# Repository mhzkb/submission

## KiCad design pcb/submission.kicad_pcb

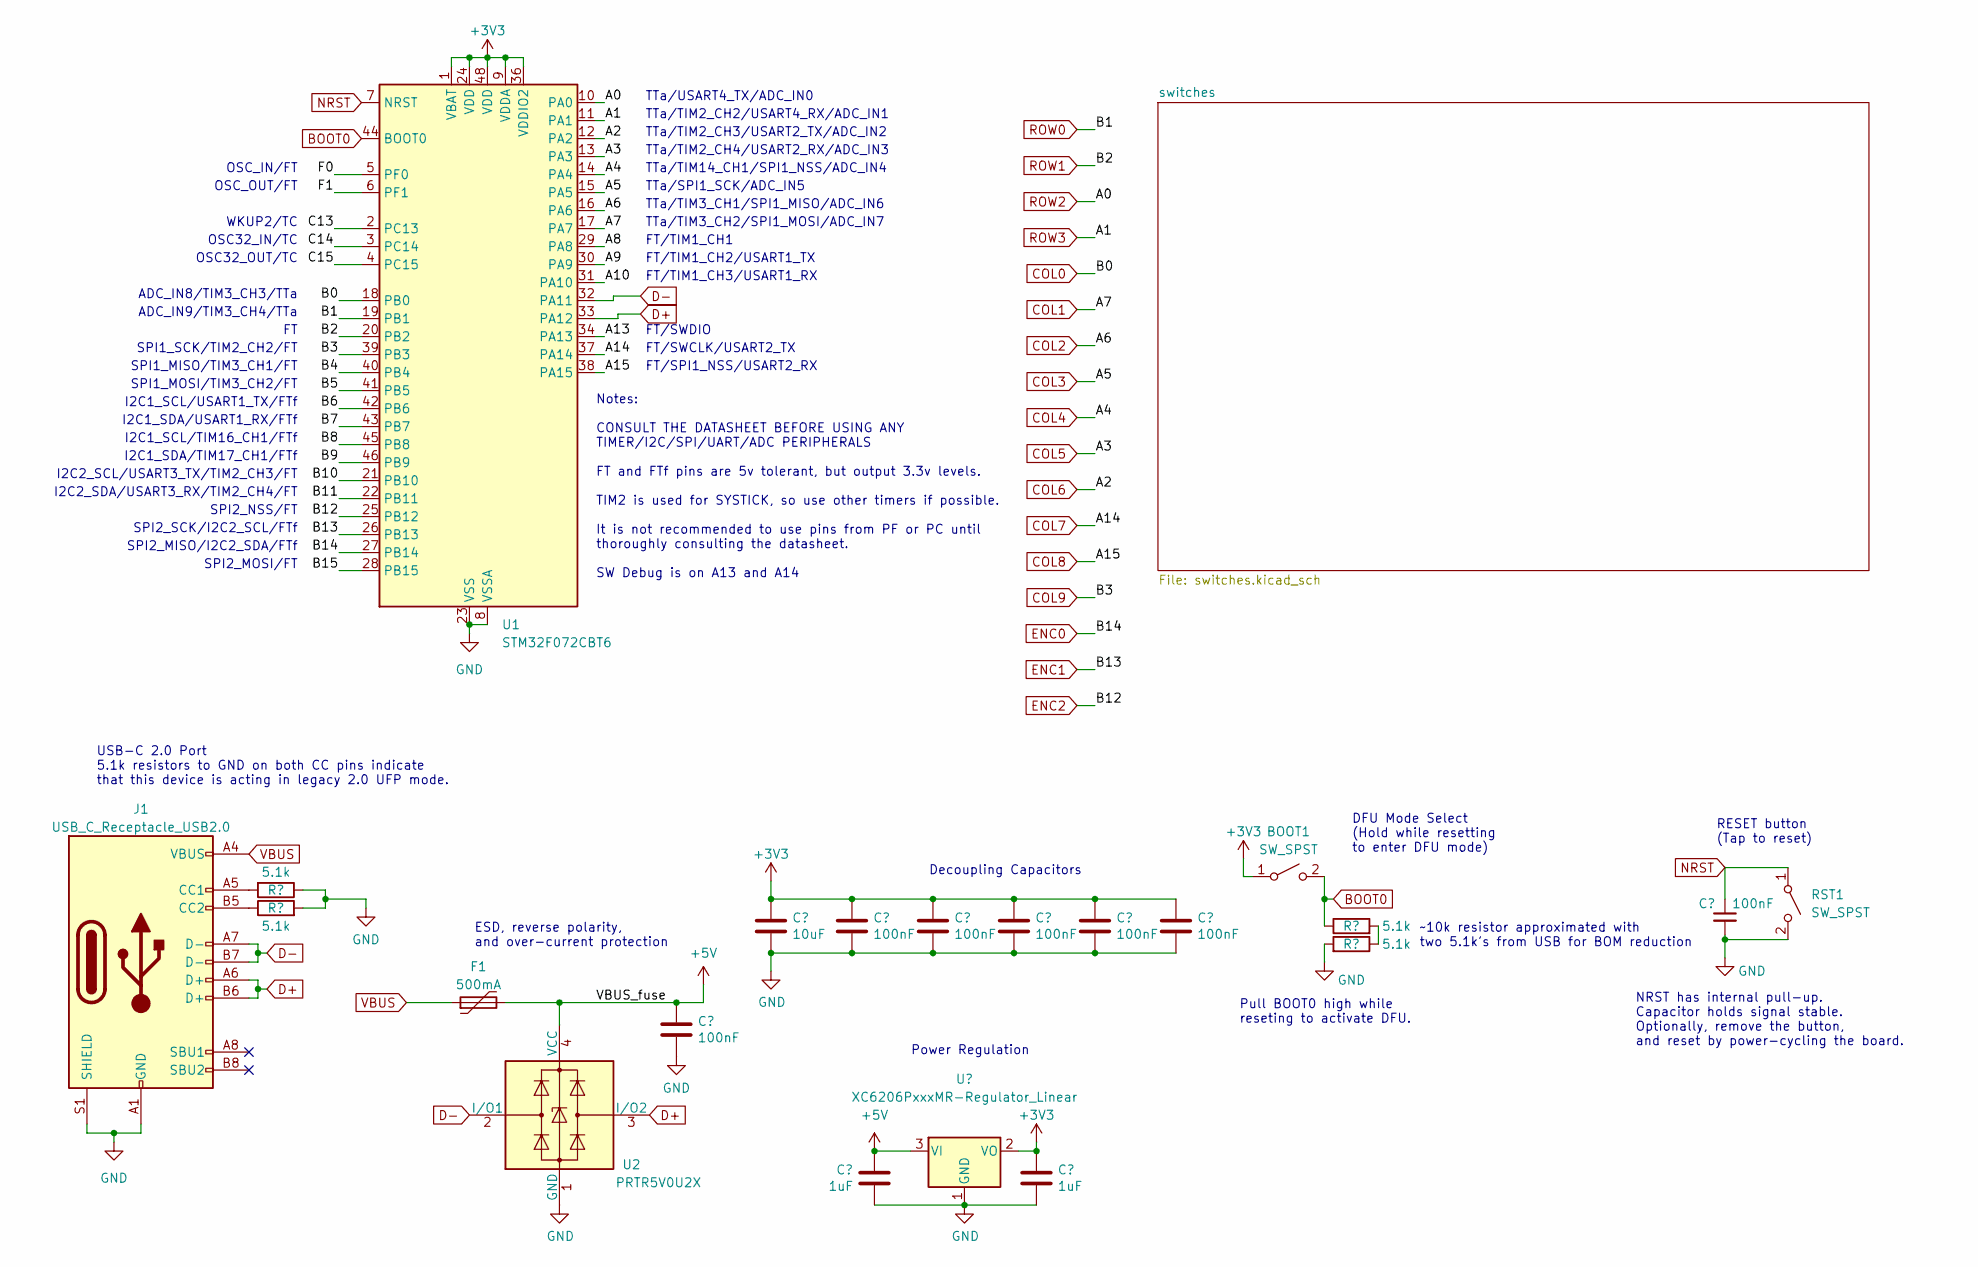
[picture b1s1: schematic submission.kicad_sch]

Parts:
BOOT1: SW_SPST; SW_SPST_TL3342
C1, C3, C4, C5, C6, C7, C8: 100nF; C_0402_1005Metric; LCSC C307331
C2: 10uF; C_0603_1608Metric; LCSC C307331
C9, C10: 1uF; C_0402_1005Metric; LCSC C307331
F1: 500mA; Fuse_1206_3216Metric; LCSC C135341
J1: USB_C_Receptacle_USB2.0; USB_C_Receptacle_HRO_TYPE-C-31-M-12; JlcRotOffset 180
R1, R2, R3, R4: 5.1k; R_0402_1005Metric
RST1: SW_SPST; SW_SPST_TL3342
U1: STM32F072CBT6; LQFP-48_7x7mm_P0.5mm; JlcRotOffset 90
U2: PRTR5V0U2X; SOT-143; LCSC C2827688
U3: XC6206PxxxMR-Regulator_Linear; SOT-23; LCSC C5446

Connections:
+3V3: BOOT1.1 (A), C2.1, C3.1, C4.1, C5.1, C6.1, C7.1, C10.1, U1.1 (VBAT), U1.9 (VDDA), U1.24 (VDD), U1.36 (VDDIO2), U1.48 (VDD), U3.2 (VO)
+5V: C8.1, C9.1, F1.2, U2.4 (VCC), U3.3 (VI)
/A8: U1.29 (PA8)
/A9: U1.30 (PA9)
/A10: U1.31 (PA10)
/A13: U1.34 (PA13)
/B4: U1.40 (PB4)
/B5: U1.41 (PB5)
/B6: U1.42 (PB6)
/B7: U1.43 (PB7)
/B8: U1.45 (PB8)
/B9: U1.46 (PB9)
/B10: U1.21 (PB10)
/B11: U1.22 (PB11)
/B15: U1.28 (PB15)
/C13: U1.2 (PC13)
/C14: U1.3 (PC14)
/C15: U1.4 (PC15)
/F0: U1.5 (PF0)
/F1: U1.6 (PF1)
BOOT0: BOOT1.2 (B), R3.1, U1.44 (BOOT0)
COL0: U1.18 (PB0); also elsewhere on the board
COL1: U1.17 (PA7); also elsewhere on the board
COL2: U1.16 (PA6); also elsewhere on the board
COL3: U1.15 (PA5); also elsewhere on the board
COL4: U1.14 (PA4); also elsewhere on the board
COL5: U1.13 (PA3); also elsewhere on the board
COL6: U1.12 (PA2); also elsewhere on the board
COL7: U1.37 (PA14); also elsewhere on the board
COL8: U1.38 (PA15); also elsewhere on the board
COL9: U1.39 (PB3); also elsewhere on the board
D+: J1.A6 (D+), J1.B6 (D+), U1.33 (PA12), U2.3 (I/O2)
D-: J1.A7 (D-), J1.B7 (D-), U1.32 (PA11), U2.2 (I/O1)
ENC0: U1.27 (PB14); also elsewhere on the board
ENC1: U1.26 (PB13); also elsewhere on the board
ENC2: U1.25 (PB12); also elsewhere on the board
GND: C1.2, C2.2, C3.2, C4.2, C5.2, C6.2, C7.2, C8.2, C9.2, C10.2, J1.A1 (GND), J1.A12 (GND), J1.B1 (GND), J1.B12 (GND), J1.S1 (SHIELD), R1.1, R2.2, R4.2, RST1.2 (B), U1.8 (VSSA), U1.23 (VSS), U1.35 (VSS), U1.47 (VSS), U2.1 (GND), U3.1 (GND); also elsewhere on the board
NRST: C1.1, RST1.1 (A), U1.7 (NRST)
unnamed: J1.A5 (CC1), R1.2
unnamed: J1.B5 (CC2), R2.1
unnamed: R3.2, R4.1
ROW0: U1.19 (PB1); also elsewhere on the board
ROW1: U1.20 (PB2); also elsewhere on the board
ROW2: U1.10 (PA0); also elsewhere on the board
ROW3: U1.11 (PA1); also elsewhere on the board
VBUS: F1.1, J1.A4 (VBUS), J1.A9 (VBUS), J1.B4 (VBUS), J1.B9 (VBUS)

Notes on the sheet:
SPI1_SCK/TIM2_CH2/FT
FT/TIM1_CH1
FT/TIM1_CH3/USART1_RX
SPI2_NSS/FT
Notes: CONSULT THE DATASHEET BEFORE USING ANY TIMER/I2C/SPI/UART/ADC PERIPHERALS FT and FTf pins are 5v tolerant, but output 3.3v levels. TIM2 is used for SYSTICK, so use other timers if possible. It is not recommended to use pins from PF or PC until thoroughly consulting the datasheet. SW Debug is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
TTa/TIM2_CH4/USART2_RX/ADC_IN3
NRST has internal pull-up. Capacitor holds signal stable. Optionally, remove the button, and reset by power-cycling the board.
FT/SWDIO
Decoupling Capacitors
SPI1_MOSI/TIM3_CH2/FT
ADC_IN9/TIM3_CH4/TTa
I2C2_SCL/USART3_TX/TIM2_CH3/FT
SPI2_MISO/I2C2_SDA/FTf
FT/SWCLK/USART2_TX
I2C1_SCL/TIM16_CH1/FTf
~10k resistor approximated with two 5.1k's from USB for BOM reduction
TTa/TIM2_CH2/USART4_RX/ADC_IN1
USB-C 2.0 Port 5.1k resistors to GND on both CC pins indicate that this device is acting in legacy 2.0 UFP mode.
TTa/TIM2_CH3/USART2_TX/ADC_IN2
OSC_IN/FT
DFU Mode Select (Hold while resetting to enter DFU mode)
WKUP2/TC
I2C2_SDA/USART3_RX/TIM2_CH4/FT
ADC_IN8/TIM3_CH3/TTa
RESET button (Tap to reset)
Pull BOOT0 high while reseting to activate DFU.
I2C1_SDA/TIM17_CH1/FTf
TTa/SPI1_SCK/ADC_IN5
TTa/TIM3_CH1/SPI1_MISO/ADC_IN6
TTa/TIM3_CH2/SPI1_MOSI/ADC_IN7
OSC32_OUT/TC
FT/SPI1_NSS/USART2_RX
SPI1_MISO/TIM3_CH1/FT
OSC32_IN/TC
TTa/TIM14_CH1/SPI1_NSS/ADC_IN4
I2C1_SDA/USART1_RX/FTf
SPI2_MOSI/FT
FT/TIM1_CH2/USART1_TX
Power Regulation
SPI2_SCK/I2C2_SCL/FTf

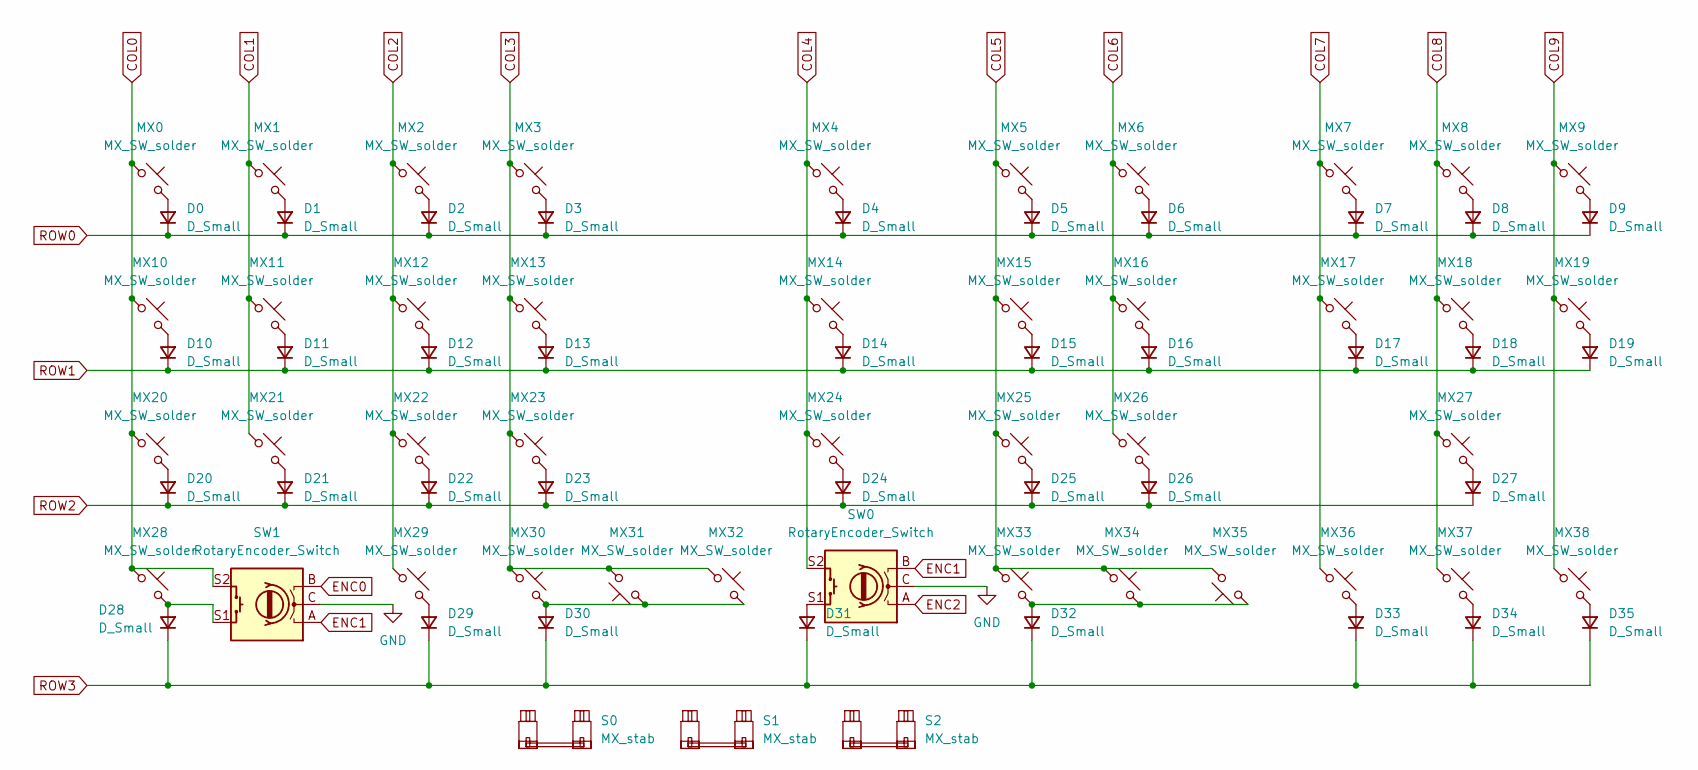
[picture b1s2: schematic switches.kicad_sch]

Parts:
D0, D1, D2, D3, D4, D5, D6, D7, D8, D9, D10, D11, D12, D13, D14, D15, D16, D17, D18, D19, D20, D21, D22, D23, D24, D25, D26, D27, D28, D29, D30, D31, D32, D33, D34, D35: D_Small; D_SOD-123
MX0, MX1, MX2, MX3, MX4, MX5, MX6, MX7, MX8, MX9, MX11, MX12, MX13, MX14, MX15, MX16, MX17, MX18, MX19, MX21, MX22, MX23, MX24, MX25, MX26, MX27, MX31, MX32, MX34, MX35, MX36, MX37, MX38: MX_SW_solder; SW_MX_1u
MX10, MX20, MX28, MX29: MX_SW_solder; SW_MX_1.25u
MX30, MX33: MX_SW_solder; SW_MX_1.5u
S0: MX_stab; STAB_MX_P_3u
S1, S2: MX_stab; STAB_MX_P_2u
SW0, SW1: RotaryEncoder_Switch; RotaryEncoder_EC11

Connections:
COL0: MX0.1, MX10.1, MX20.1, MX28.1, SW1.S2; also elsewhere on the board
COL1: MX1.1, MX11.1, MX21.1; also elsewhere on the board
COL2: MX2.1, MX12.1, MX22.1, MX29.1; also elsewhere on the board
COL3: MX3.1, MX13.1, MX23.1, MX30.1, MX31.2, MX32.1; also elsewhere on the board
COL4: MX4.1, MX14.1, MX24.1, SW0.S2; also elsewhere on the board
COL5: MX5.1, MX15.1, MX25.1, MX33.1, MX34.1, MX35.2; also elsewhere on the board
COL6: MX6.1, MX16.1, MX26.1; also elsewhere on the board
COL7: MX7.1, MX17.1, MX36.1; also elsewhere on the board
COL8: MX8.1, MX18.1, MX27.1, MX37.1; also elsewhere on the board
COL9: MX9.1, MX19.1, MX38.1; also elsewhere on the board
ENC0: SW1.B; also elsewhere on the board
ENC1: SW0.B, SW1.A; also elsewhere on the board
ENC2: SW0.A; also elsewhere on the board
GND: SW0.C, SW1.C; also elsewhere on the board
unnamed: D0.2 (A), MX0.2
unnamed: D1.2 (A), MX1.2
unnamed: D2.2 (A), MX2.2
unnamed: D3.2 (A), MX3.2
unnamed: D4.2 (A), MX4.2
unnamed: D5.2 (A), MX5.2
unnamed: D6.2 (A), MX6.2
unnamed: D7.2 (A), MX7.2
unnamed: D8.2 (A), MX8.2
unnamed: D9.2 (A), MX9.2
unnamed: D10.2 (A), MX10.2
unnamed: D11.2 (A), MX11.2
unnamed: D12.2 (A), MX12.2
unnamed: D13.2 (A), MX13.2
unnamed: D14.2 (A), MX14.2
unnamed: D15.2 (A), MX15.2
unnamed: D16.2 (A), MX16.2
unnamed: D17.2 (A), MX17.2
unnamed: D18.2 (A), MX18.2
unnamed: D19.2 (A), MX19.2
unnamed: D20.2 (A), MX20.2
unnamed: D21.2 (A), MX21.2
unnamed: D22.2 (A), MX22.2
unnamed: D23.2 (A), MX23.2
unnamed: D24.2 (A), MX24.2
unnamed: D25.2 (A), MX25.2
unnamed: D26.2 (A), MX26.2
unnamed: D27.2 (A), MX27.2
unnamed: D28.2 (A), MX28.2, SW1.S1
unnamed: D29.2 (A), MX29.2
unnamed: D30.2 (A), MX30.2, MX31.1, MX32.2
unnamed: D31.2 (A), SW0.S1
unnamed: D32.2 (A), MX33.2, MX34.2, MX35.1
unnamed: D33.2 (A), MX36.2
unnamed: D34.2 (A), MX37.2
unnamed: D35.2 (A), MX38.2
ROW0: D0.1 (K), D1.1 (K), D2.1 (K), D3.1 (K), D4.1 (K), D5.1 (K), D6.1 (K), D7.1 (K), D8.1 (K), D9.1 (K); also elsewhere on the board
ROW1: D10.1 (K), D11.1 (K), D12.1 (K), D13.1 (K), D14.1 (K), D15.1 (K), D16.1 (K), D17.1 (K), D18.1 (K), D19.1 (K); also elsewhere on the board
ROW2: D20.1 (K), D21.1 (K), D22.1 (K), D23.1 (K), D24.1 (K), D25.1 (K), D26.1 (K), D27.1 (K); also elsewhere on the board
ROW3: D28.1 (K), D29.1 (K), D30.1 (K), D31.1 (K), D32.1 (K), D33.1 (K), D34.1 (K), D35.1 (K); also elsewhere on the board

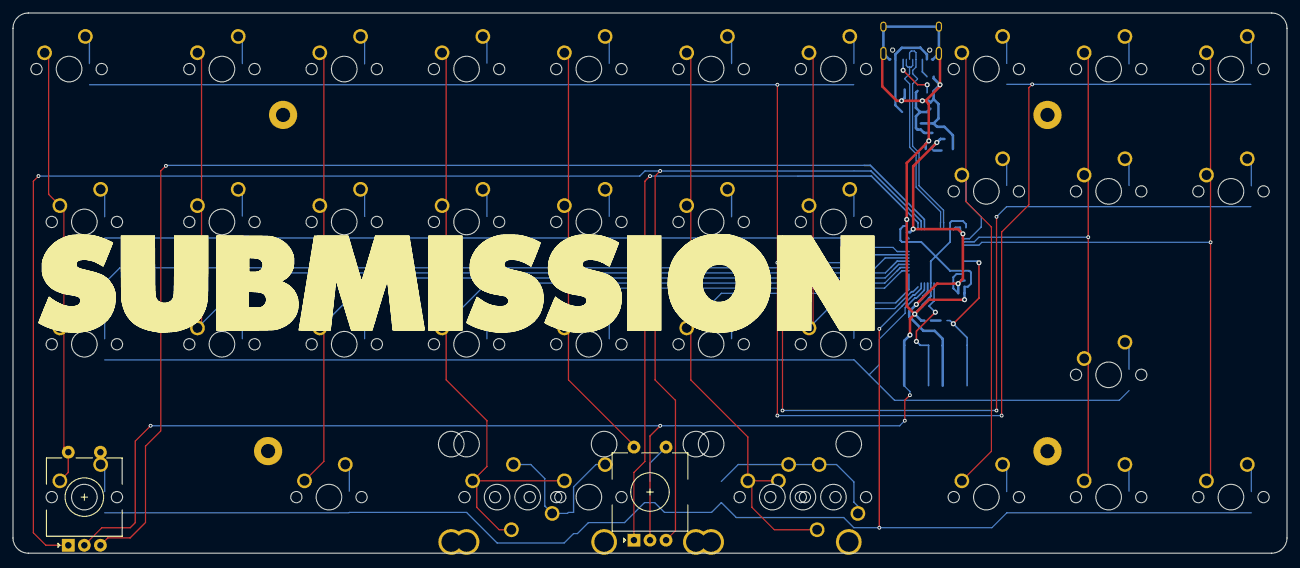
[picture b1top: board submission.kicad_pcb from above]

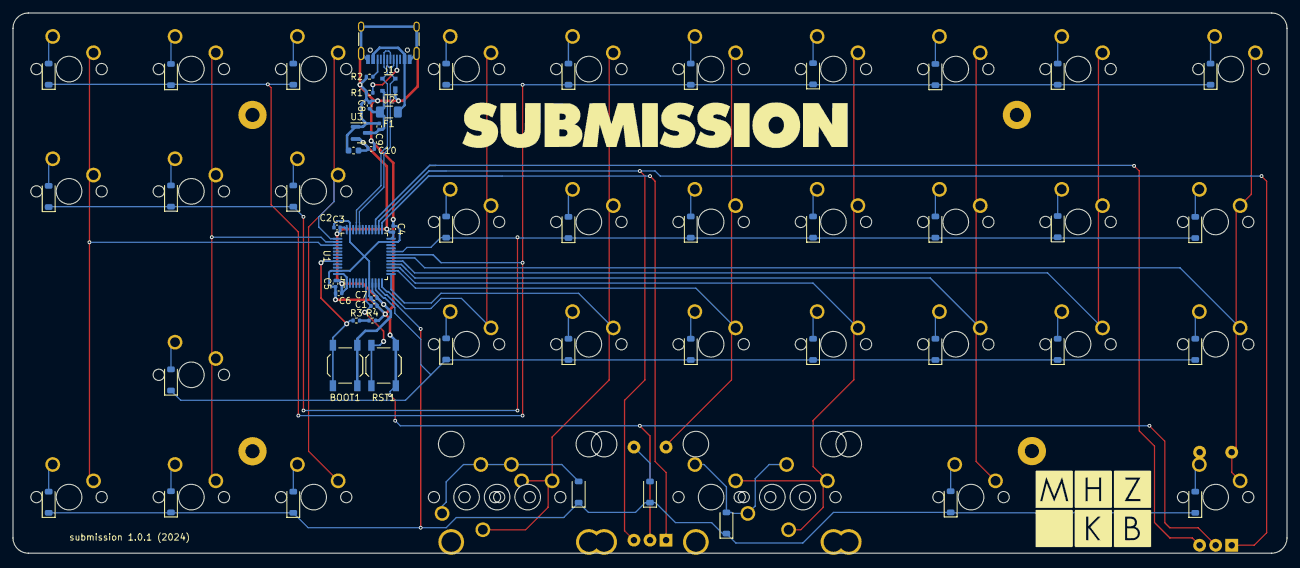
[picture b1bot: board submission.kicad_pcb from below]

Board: 2 copper layers, 198.4 x 84.1 mm, 101 parts (57 on the bottom side), 64 nets.

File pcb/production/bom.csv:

Designator,Footprint,Quantity,Value,LCSC Part #
"BOOT1, RST1",SW_SPST_TL3342,2,SW_SPST,C318884
"C1, C3, C4, C5, C6, C7, C8",402,7,100nF,C1546
"C10, C9",402,2,1uF,C52923
C2,603,1,10uF,C19702
"D0, D1, D10, D11, D12, D13, D14, D15, D16, D17, D18, D19, D2, D20, D21, D22, D23, D24, D25, D26, D27, D28, D29, D3, D30, D31, D32, D33, D34, D35, D4, D5, D6, D7, D8, D9",D_SOD-123,36,D_Small,C2972760
F1,1206,1,500mA,C369160
J1,USB_C_Receptacle_HRO_TYPE-C-31-M-12,1,USB_C_Receptacle_USB2.0,C165948
"R1, R2, R3, R4",402,4,5.1k,C25905
U1,LQFP-48_7x7mm_P0.5mm,1,STM32F072CBT6,C81720
U2,SOT-143,1,PRTR5V0U2X,C2827688
U3,SOT-23,1,XC6206PxxxMR-Regulator_Linear,C5446

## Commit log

2024-10-07 Added pre-compiled Vial keymap.
2024-10-07 Updated README.
2025-06-15 Added case source file.
2025-06-21 Converted case to single size (6x3 mm) magnets.
2025-06-23 Added alternative bottom styles.
2025-10-24 Added Kicad project and export files
2026-05-04 Updated pcb silkscreen
2026-05-04 Added missing matrix schematic
2026-05-04 Added submission plate files
